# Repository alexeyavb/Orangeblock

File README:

Wh is need:
WeAct studio Black pill stm32f411ceu6
Any working pcm5102 shield configured as slave in i2s Phillips standard
Any working pcm1808 shield configured as slave in i2s Phillips standard

Big Steps for implementing
 make test board
 write firmware fo stm32
 write linux device driver for orange pi

Wh implemented as demo
 simple i2s-i2s bridge firmware for stm32 (in+out) in 48k 24bit 256fs
	opi worked as i2s master
	stm32<->opi-mcu bridge as slave with internal clocking
	stm32 i2s master reciever with internal clock and mclock/bclock output
	stm32 i2s master transmitter with internal clock and mclock/bclock utput
	clock dividers for 48/96/192K audio processing and internal i2s pll reconf +- 0.04% clock error

 simple stm32-i2s kernel audio device driver for use ALSA/JACKd (audio in and audio out)
 simple overlay for enabling i2s in Orange PI PC/ONE in 40pin GPIO header. Implement as 48k 24bit 256fs only without bclck change

Complete tracing shield

[test board photo1]
[test board photo2]
[test board photo3]
[test board photo4]

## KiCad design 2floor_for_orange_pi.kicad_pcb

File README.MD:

*Why is need:*

* WeAct studio Black pill stm32f411ceu6
* Any working pcm5102 shield configured as slave in i2s Phillips standard
* Any working pcm1808 shield configured as slave in i2s Phillips standard

**Big Steps for implementing**
+ make test board
+ write firmware fo stm32
+ write in/out audio  overlay for linux dts tree
+ write linux device driver for orange pi

**Wh implemented as demo**
+ simple i2s-i2s bridge firmware for stm32 (in+out) in 48k 24bit 256fs
+ opi worked as i2s master
+ stm32<->opi-mcu bridge as slave with internal clocking
+ stm32 i2s master reciever with internal clock and mclock/bclock output
+ stm32 i2s master transmitter with internal clock and mclock/bclock utput
+ clock dividers for 48/96/192K audio processing and internal i2s pll reconf +- 0.04% clock error

- simple stm32-i2s kernel audio device driver for use ALSA/JACKd (audio in and audio out)
- simple overlay for enabling i2s in Orange PI PC/ONE in 40pin GPIO header. Implement as 48k 24bit 256fs only without bclck change

* **20241031** Complete tracing shield
* **20241107** received factory printed boards

2024/Nov/08
* Received printed PCB

2024/Nov/09
* Soldered sockets anmd pins

+ ***Process Testing with STM32 board***

* Testing with simple i2s hardware-factory-slave with fs autodetection configured i2s ADC 24bit pcm1808 (board from ChipDip DAC)
command: 

  ****$arecord -t raw -D "hw:1,0" -V stereo -c 2 -f S24_LE -r 32000 -d 400 -v --dump-hw-params --disable-resample ~/002-test24.dat****

+ ***raw folder contained raw i2s 24bit 48k data and mp3 ()***
    +raw i2s data in folder ./docs/Conn_And_Tests/ADC_20241109/results/002-test24.dat
    +mp3 data in folder ./docs/Conn_And_Tests/ADC_20241109/results/002-test24.mp3
2024/Nov/17
* Added OPI SPI kernel overlay

+ Found issue with UART OPI positions

***remarks***
There was an error in placing the socket for 3PIN UART socket from orange PI to shield. This will not interfere with functionality, but will be fixed in the next version of the board.

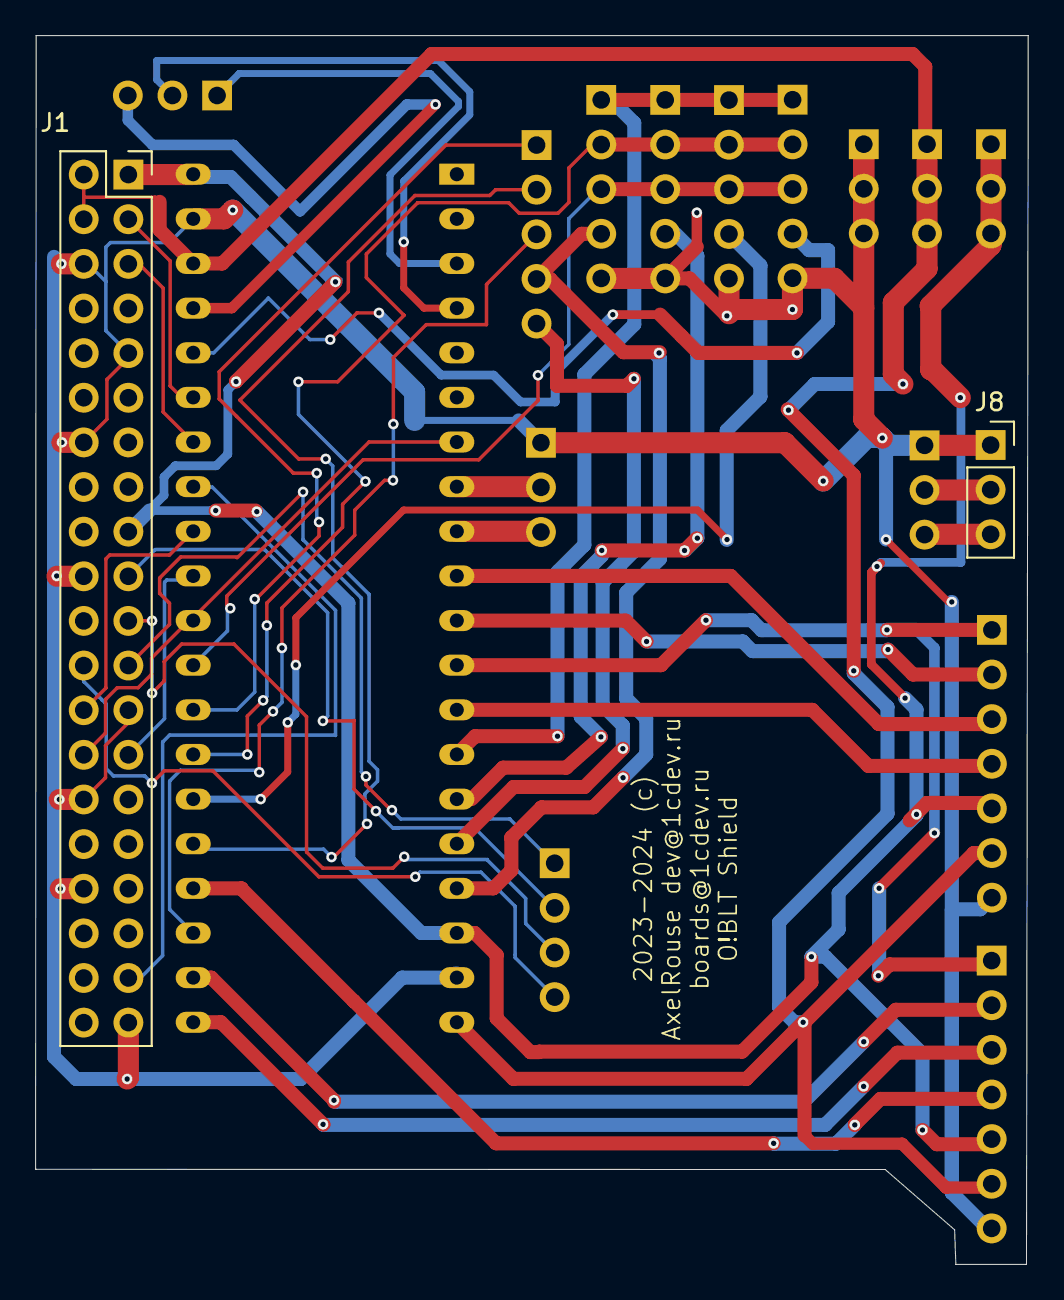
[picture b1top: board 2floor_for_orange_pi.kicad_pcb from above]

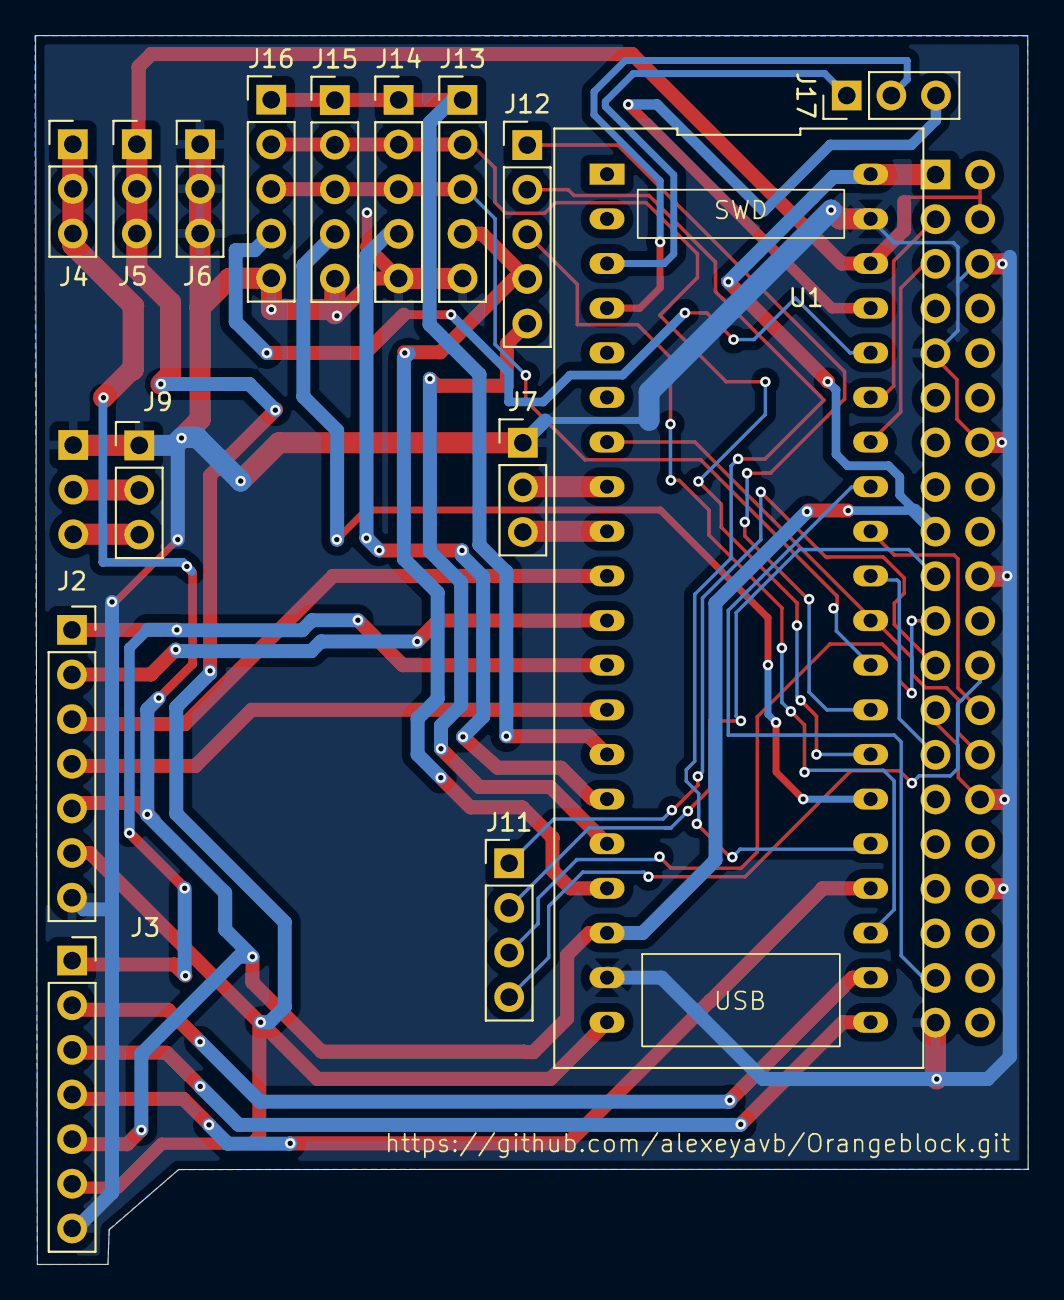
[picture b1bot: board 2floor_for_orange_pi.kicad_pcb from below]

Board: 2 copper layers, 56.5 x 69.9 mm, 17 parts (15 on the bottom side), 36 nets.

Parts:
J1: Orange_PI_PC_ONE_40Pin_Header; PinSocket_2x20_P2.54mm_Vertical
J2: I2S1 DAC Socket; PinSocket_1x07_P2.54mm_Vertical
J3: I2S2 ADC Socket; PinSocket_1x07_P2.54mm_Vertical
J4: +3V3 Header; PinHeader_1x03_P2.54mm_Vertical
J5: +5V Header; PinHeader_1x03_P2.54mm_Vertical
J6: GND Header; PinHeader_1x03_P2.54mm_Vertical
J7: STM32 DEBUG Header; PinHeader_1x03_P2.54mm_Vertical
J8: OPI Conn Debug Socket; PinSocket_1x03_P2.54mm_Vertical
J9: OPI Conn Debug Header; PinHeader_1x03_P2.54mm_Vertical
J11: OPI SPI0 Header; PinHeader_1x04_P2.54mm_Vertical
J12: ST7735 Header; PinHeader_1x05_P2.54mm_Vertical
J13, J14, J15, J16: SPI5 Header; PinHeader_1x05_P2.54mm_Vertical
J17: STM32 GPIO Header; PinHeader_1x03_P2.54mm_Vertical
U1: STM32_WeActSt_BlackPill

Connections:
+3V3: J1.1 (3V3), J1.17 (3V3), J2.5, J3.5, J4.1, J4.2, J4.3, U1.18 (3V3), U1.40 (3V3)
+5V: J1.2 (5V), J1.4 (5V), J2.6, J3.6, J5.1, J5.2, J5.3, U1.20 (5v), U1.38 (5v)
/I2S1_BCK: J2.2, U1.11 (A5)
/I2S1_Data_Out: J2.4, U1.13 (A7)
/I2S1_LRCK: J2.3, U1.10 (A4)
/I2S2_BCK: J3.2, U1.22 (B13)
/I2S2_DATA_IN: J3.4, U1.24 (B15)
/I2S2_LRCK: J3.3, U1.21 (B12)
/I2S2_SCK: J2.1, J3.1, U1.12 (A6)
/PCM0_CLCK: J1.27 ((PA19)), U1.31 (B3)
/PCM0_DIN: J1.26 ((PA21)), U1.32 (B4)
/PCM0_DOUT: J1.37 ((PA20)/PA20), U1.33 (B5)
/PCM0_SYNC: J1.28 ((PA18)), U1.7 (A1), U1.30 (A15)
/SPI5_CS1: J14.4, U1.15 (B1)
/SPI5_CS2: J15.4, U1.26 (A9)
/SPI5_CS3: J16.4, U1.36 (B8)
/SPI5_MISO: J13.3, J14.3, J15.3, J16.3, U1.29 (A12)
/SPI5_MOSI: J13.2, J14.2, J15.2, J16.2, U1.27 (A10)
/SPI5_SCK: J13.1, J14.1, J15.1, J16.1, U1.14 (B0)
/ST7735_BL: J12.2, U1.25 (A8)
/ST7735_CS: J12.4, J13.4, U1.17 (B10)
/ST7735_DC: J12.3, U1.23 (B14)
/ST7735_RES: J12.5, U1.16 (B2)
/TIM1_PWM_OUTPUT: J12.1, U1.28 (A11)
/UART_RX: J7.3, U1.9 (A3)
/UART_TX: J7.2, U1.8 (A2)
GND: J1.6 (GND), J1.9 (GND), J1.14 (GND), J1.20 (GND), J1.25 (GND), J1.30 (GND), J1.34 (GND), J1.39 (GND), J2.7, J3.7, J6.1, J6.2, J6.3, J7.1, J8.1, J9.1, J13.5, J14.5, J15.5, J16.5, U1.19 (G), U1.39 (G)
unnamed: J1.5 ((PA11)/TWI0_SCK), U1.34 (B6)
unnamed: J1.3 ((PA12)/TWI0_SDA), U1.35 (B7)
unnamed: J1.19 ((PC0)/SPI0_MOSI), J11.2
unnamed: J1.21 ((PC1)/SPI0_MISO), J11.3
unnamed: J1.23 ((PC2)/SPI0_SCK), J11.1
unnamed: J1.24 ((PC3}/SPI0_CS), J11.4
unnamed: J17.3, U1.37 (B9)
unnamed: J17.1, U1.3 (C14)
unnamed: J17.2, U1.4 (C15)

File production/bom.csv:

Designator,Footprint,Quantity,Value,LCSC Part #
J1,PinSocket_2x20_P2.54mm_Vertical,1,Orange_PI_PC_ONE_40Pin_Header,
J11,PinHeader_1x04_P2.54mm_Vertical,1,OPI SPI0 Header,
J12,PinHeader_1x05_P2.54mm_Vertical,1,ST7735 Header,
"J13, J14, J15, J16",PinHeader_1x05_P2.54mm_Vertical,4,SPI5 Header,
J17,PinHeader_1x03_P2.54mm_Vertical,1,STM32 GPIO Header,
J2,PinSocket_1x07_P2.54mm_Vertical,1,I2S1 DAC Socket,
J3,PinSocket_1x07_P2.54mm_Vertical,1,I2S2 ADC Socket,
J4,PinHeader_1x03_P2.54mm_Vertical,1,+3V3 Header,
J5,PinHeader_1x03_P2.54mm_Vertical,1,+5V Header,
J6,PinHeader_1x03_P2.54mm_Vertical,1,GND Header,
J7,PinHeader_1x03_P2.54mm_Vertical,1,STM32 DEBUG Header,
J8,PinSocket_1x03_P2.54mm_Vertical,1,OPI Conn Debug Socket,
J9,PinHeader_1x03_P2.54mm_Vertical,1,OPI Conn Debug Header,
U1,STM32_WeActSt_BlackPill,1,~,

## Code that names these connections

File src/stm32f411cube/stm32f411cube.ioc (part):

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Mcu.Name=STM32F411C(C-E)Ux
Mcu.Package=UFQFPN48
Mcu.UserName=STM32F411CEUx
PA0-WKUP.GPIOParameters=GPIO_PuPd,GPIO_Label
PA0-WKUP.GPIO_Label=BUTTON_KEY
PA0-WKUP.GPIO_PuPd=GPIO_PULLDOWN
PA0-WKUP.Signal=GPXTI0
PA1.Signal=GPXTI1
PA10.Mode=Full_Duplex_Master
PA10.Signal=SPI5_MOSI
PA11.Signal=S_TIM1_CH4
PA12.Mode=Full_Duplex_Master
PA12.Signal=SPI5_MISO
PA13.Mode=Serial_Wire
PA13.Signal=SYS_JTMS-SWDIO
PA14.Mode=Serial_Wire
PA14.Signal=SYS_JTCK-SWCLK
PA15.GPIOParameters=GPIO_Speed,GPIO_Label
PA15.GPIO_Label=PCM0_SYNC
PA15.GPIO_Speed=GPIO_SPEED_FREQ_HIGH
PA15.Mode=Full_Duplex_Slave
PA15.Signal=I2S3_WS
PA2.GPIOParameters=GPIO_Label
PA2.GPIO_Label=CONSOLE_TX
PA2.Mode=Asynchronous
PA2.Signal=USART2_TX
PA3.GPIOParameters=GPIO_Label
PA3.GPIO_Label=CONSOLE_RX
PA3.Mode=Asynchronous
PA3.Signal=USART2_RX
PA4.GPIOParameters=GPIO_Speed,GPIO_Label
PA4.GPIO_Label=I2S1_LRCK
PA4.GPIO_Speed=GPIO_SPEED_FREQ_HIGH
PA4.Mode=Half_Duplex_Master
PA4.Signal=I2S1_WS
PA5.GPIOParameters=GPIO_Speed,GPIO_Label
PA5.GPIO_Label=I2S1_BCK
PA5.GPIO_Speed=GPIO_SPEED_FREQ_HIGH
PA5.Mode=Half_Duplex_Master
PA5.Signal=I2S1_CK
PA6.GPIOParameters=GPIO_Speed,GPIO_Label
PA6.GPIO_Label=I2S2_SCK
PA6.GPIO_Speed=GPIO_SPEED_FREQ_HIGH
PA6.Mode=Master_Clock_Activated
PA6.Signal=I2S2_MCK
PA7.GPIOParameters=GPIO_Speed,GPIO_Label
PA7.GPIO_Label=I2S1_DATA_OUT
PA7.GPIO_Speed=GPIO_SPEED_FREQ_HIGH
PA7.Mode=Half_Duplex_Master
PA7.Signal=I2S1_SD
PA8.GPIOParameters=GPIO_Label
PA8.GPIO_Label=ST7735_BL
PA8.Signal=GPIO_Output
PA9.GPIOParameters=GPIO_Label
PA9.GPIO_Label=SPI5_CS2
PA9.Signal=GPIO_Output
PB0.Mode=Full_Duplex_Master
PB0.Signal=SPI5_SCK
PB1.GPIOParameters=GPIO_Label
PB1.GPIO_Label=SPI5_CS1
PB1.Signal=GPIO_Output
PB10.GPIOParameters=GPIO_Label
PB10.GPIO_Label=ST7735_CS
PB10.Signal=GPIO_Output
PB12.GPIOParameters=GPIO_Speed,GPIO_Label
PB12.GPIO_Label=I2S2_LRCK
PB12.GPIO_Speed=GPIO_SPEED_FREQ_LOW
PB12.Mode=Half_Duplex_Master
PB12.Signal=I2S2_WS
PB13.GPIOParameters=GPIO_Speed,GPIO_Label
PB13.GPIO_Label=I2S2_BCK
PB13.GPIO_Speed=GPIO_SPEED_FREQ_HIGH
PB13.Mode=Half_Duplex_Master
PB13.Signal=I2S2_CK
PB14.GPIOParameters=GPIO_Label
PB14.GPIO_Label=ST7735_DC
PB14.Signal=GPIO_Output
PB15.GPIOParameters=GPIO_Speed,GPIO_Label
PB15.GPIO_Label=I2S2_DATA_IN
PB15.GPIO_Speed=GPIO_SPEED_FREQ_MEDIUM
PB15.Mode=Half_Duplex_Master
PB15.Signal=I2S2_SD
PB2.GPIOParameters=GPIO_Label
PB2.GPIO_Label=ST7735_RES
PB2.Signal=GPIO_Output
PB3.GPIOParameters=GPIO_Speed,GPIO_Label
PB3.GPIO_Label=PCM0_CLK
PB3.GPIO_Speed=GPIO_SPEED_FREQ_HIGH
PB3.Mode=Full_Duplex_Slave
PB3.Signal=I2S3_CK
PB4.GPIOParameters=GPIO_Speed,GPIO_Label
PB4.GPIO_Label=PCM0_OUT
PB4.GPIO_Speed=GPIO_SPEED_FREQ_HIGH
PB4.Mode=Full_Duplex_Slave
PB4.Signal=I2S3_ext_SD
PB5.GPIOParameters=GPIO_Speed,GPIO_Label
PB5.GPIO_Label=PCM0_INP
PB5.GPIO_Speed=GPIO_SPEED_FREQ_MEDIUM
PB5.Mode=Full_Duplex_Slave
PB5.Signal=I2S3_SD
PB6.GPIOParameters=GPIO_Speed,GPIO_Pu
PB6.GPIO_Pu=GPIO_PULLUP
PB6.GPIO_Speed=GPIO_SPEED_FREQ_VERY_HIGH
PB6.Mode=I2C
PB6.Signal=I2C1_SCL
PB7.GPIOParameters=GPIO_Pu
PB7.GPIO_Pu=GPIO_PULLUP
PB7.Mode=I2C
PB7.Signal=I2C1_SDA
PB8.GPIOParameters=GPIO_Label
PB8.GPIO_Label=SPI5_CS3
PB8.Signal=GPIO_Output
PC13-ANTI_TAMP.GPIOParameters=PinState,GPIO_Label
PC13-ANTI_TAMP.GPIO_Label=LED_PIN
PC13-ANTI_TAMP.PinState=GPIO_PIN_RESET
PC13-ANTI_TAMP.Signal=GPIO_Output
PH0\ -\ OSC_IN.Mode=HSE-External-Oscillator
PH0\ -\ OSC_IN.Signal=RCC_OSC_IN
PH1\ -\ OSC_OUT.Mode=HSE-External-Oscillator
PH1\ -\ OSC_OUT.Signal=RCC_OSC_OUT
RCC.HSE_Timout=120
RCC.HSE_VALUE=25000000
RCC.SYSCLKFreq_VALUE=92307692.3076923
RCC.SYSCLKSource=RCC_SYSCLKSOURCE_PLLCLK
board=custom

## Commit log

2024-10-13 PCB project
2024-10-13 README added
2024-10-14 completed 1st tracing
2024-10-14 Change history
2024-10-14 rebuild
2024-10-19 sended to print
2024-11-08 dded photos of recceived PCB<F2>
2024-11-08 Added remarks to README
2024-11-08 Added reNAME A README
2024-11-08 Added README MD
2024-11-08 Any changes
2024-11-09 added sources files for board (overlay + kernel)
2024-11-09 README changes
2024-11-09 ADD more photos
2024-11-09 Added tests results
2024-11-09 Remove cyrillic symbols
2024-11-09 changed readme
2024-11-09 chage readme
2024-11-09 added Licenses
2024-11-18 add SPI-CS1 overlay
2024-11-18 Added README changes
2024-11-18 add cubemx.ioc file
2024-12-20 First version of firmware for f411
